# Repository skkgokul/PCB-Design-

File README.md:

This is a basic PCB(Printe circuit board) design of Fire alarm cricuit.
The software used in this PCB design  is ki-cad version 7.

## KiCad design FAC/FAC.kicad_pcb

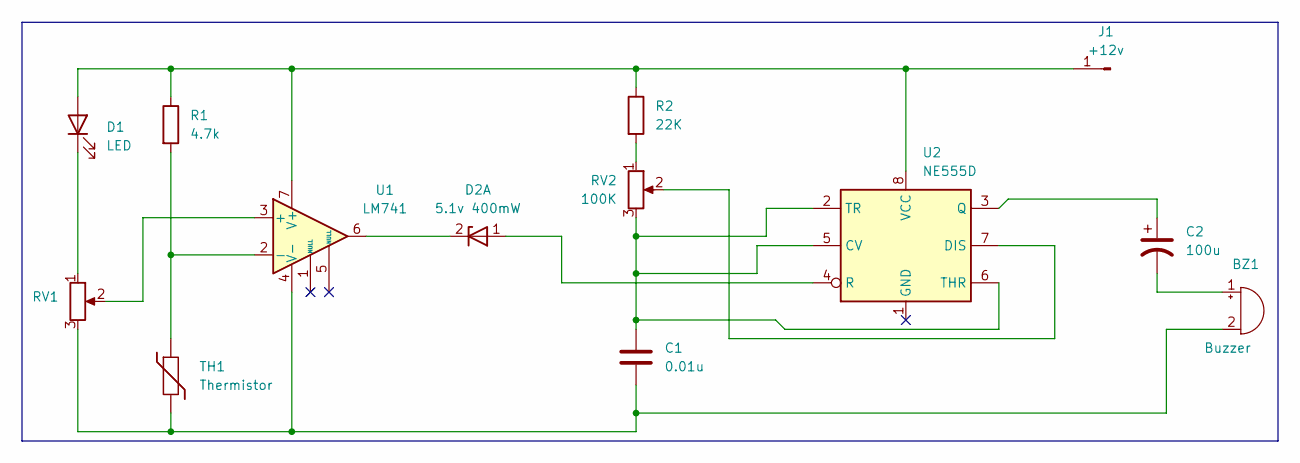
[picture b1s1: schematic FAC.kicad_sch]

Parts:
BZ1: Buzzer; Buzzer_12x9.5RM7.6
C1: 0.01u; C_Axial_L3.8mm_D2.6mm_P7.50mm_Horizontal
C2: 100u; CP_Axial_L10.0mm_D4.5mm_P15.00mm_Horizontal
D1: LED; LED_D3.0mm
D2: 5.1v 400mW; R_Axial_DIN0204_L3.6mm_D1.6mm_P7.62mm_Horizontal
J1: +12v; Hirose_DF63M-1P-3.96DSA_1x01_P3.96mm_Vertical
R1: 4.7k; R_Axial_DIN0204_L3.6mm_D1.6mm_P7.62mm_Horizontal
R2: 22K; R_Axial_DIN0204_L3.6mm_D1.6mm_P7.62mm_Horizontal
RV1: Potentiometer_ACP_CA6-H2,5_Horizontal
RV2: 100K; Potentiometer_ACP_CA6-H2,5_Horizontal
TH1: Thermistor; R_Axial_DIN0204_L3.6mm_D1.6mm_P1.90mm_Vertical
U1: LM741; DIP-8-16_W7.62mm
U2: NE555D; SOIC-8_3.9x4.9mm_P1.27mm

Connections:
unnamed: BZ1.1 (+), C2.2
unnamed: BZ1.2 (-), C1.2, RV1.3, TH1.2, U1.4 (V-)
unnamed: D1.2 (A), J1.1, R1.1, R2.1, U1.7 (V+), U2.8 (VCC)
unnamed: D1.1 (K), RV1.1
unnamed: D2.1 (A), U2.4 (R)
unnamed: D2.2 (K), U1.6
unnamed: R2.2, RV2.1
unnamed: RV1.2, U1.3 (+)
unnamed: R1.2, TH1.1, U1.2 (-)
unnamed: C1.1, RV2.3, U2.2 (TR), U2.5 (CV), U2.6 (THR)
unnamed: RV2.2, U2.7 (DIS)
unnamed: C2.1, U2.3 (Q)

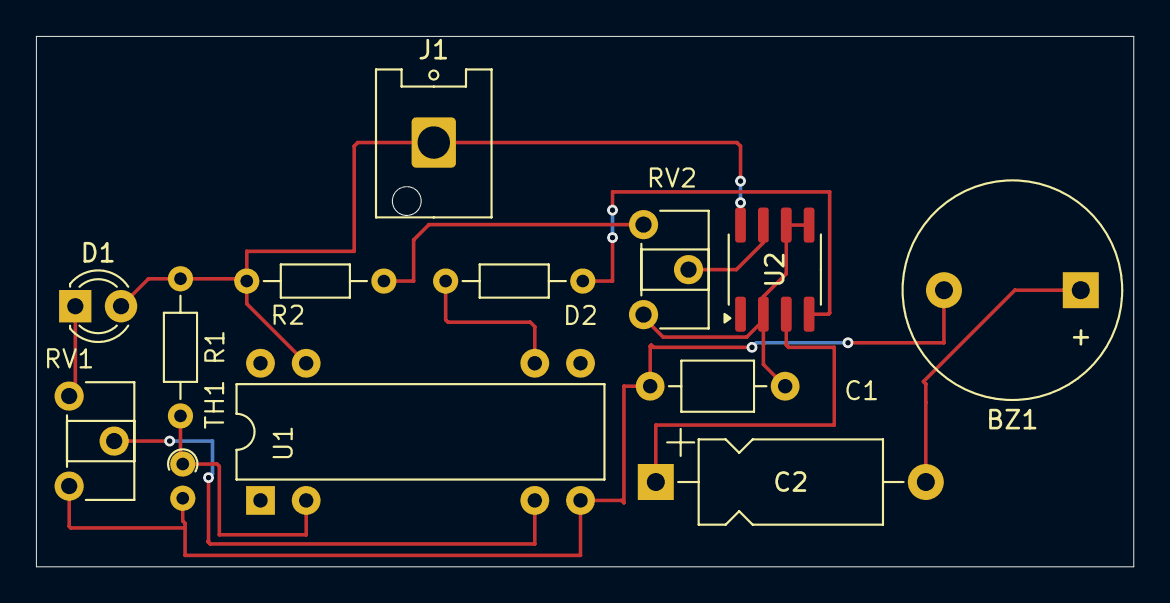
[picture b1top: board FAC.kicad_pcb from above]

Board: 2 copper layers, 61.0 x 29.5 mm, 13 parts (0 on the bottom side), 12 nets.
